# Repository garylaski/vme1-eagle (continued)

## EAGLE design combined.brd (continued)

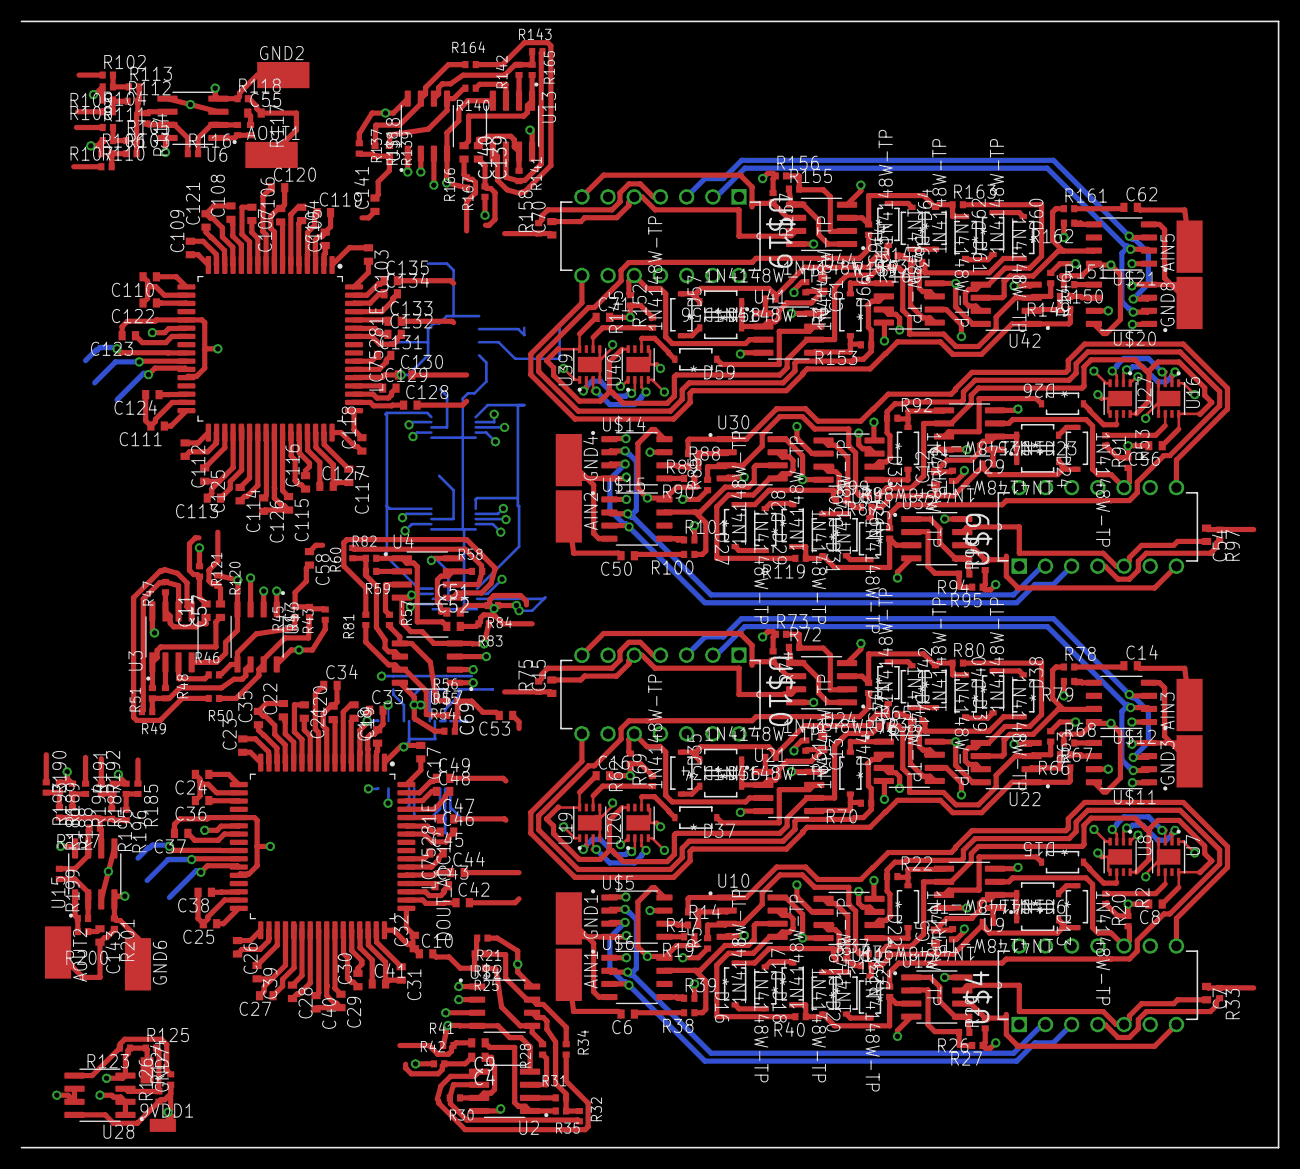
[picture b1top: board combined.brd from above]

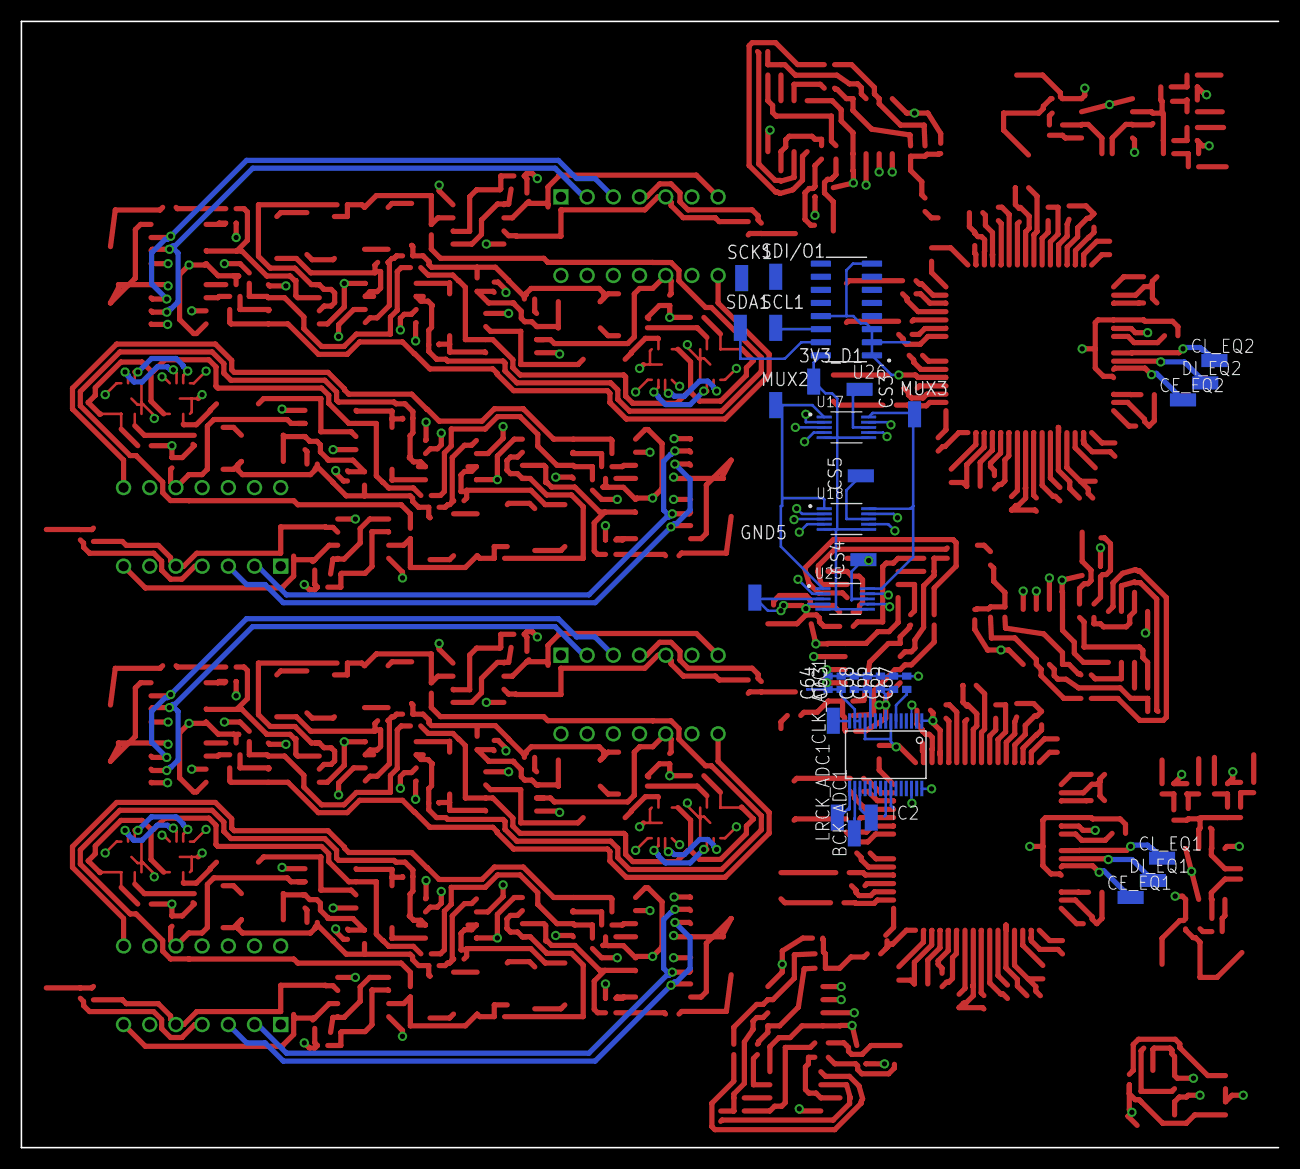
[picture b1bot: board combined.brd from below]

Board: 4 copper layers, 121.9 x 109.2 mm, 398 parts (33 on the bottom side), 337 nets.

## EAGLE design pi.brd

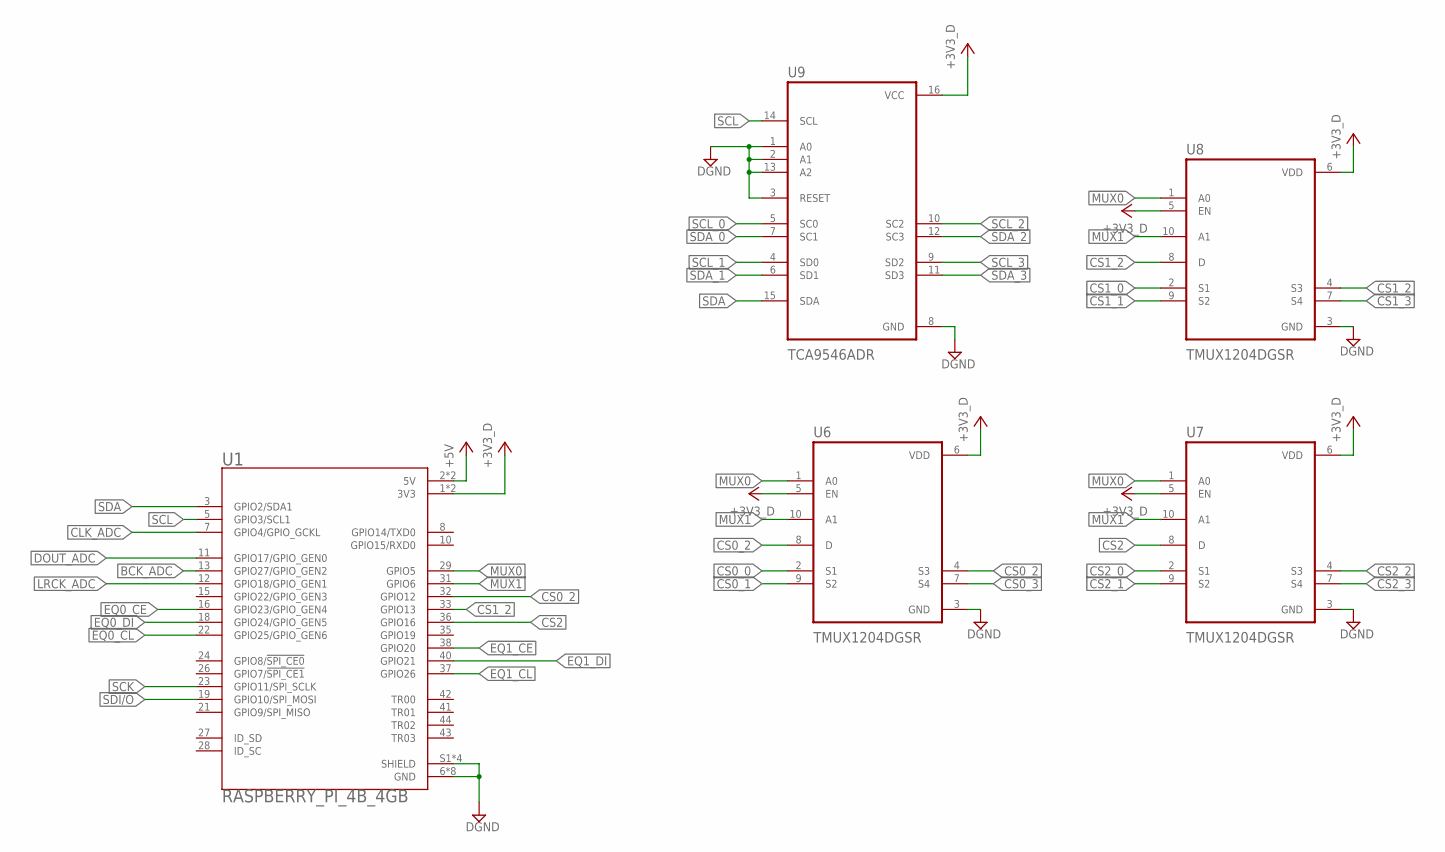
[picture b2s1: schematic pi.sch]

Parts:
U1: RASPBERRY_PI_4B_4GB; MODULE_RASPBERRY_PI_4B_4GB
U6, U7, U8: TMUX1204DGSR; SOP50P490X110-10N
U9: TCA9546ADR; SOIC127P600X175-16N

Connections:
5V: U1.2 (5V), U1.4 (5V)
+3V3: U1.1 (3V3), U1.17 (3V3), U6.5 (EN), U6.6 (VDD), U7.5 (EN), U7.6 (VDD), U8.5 (EN), U8.6 (VDD), U9.16 (VCC)
BCK_ADC: U1.13 (GPIO27/GPIO_GEN2)
CLK_ADC: U1.7 (GPIO4/GPIO_GCKL)
CS0_0: U6.2 (S1)
CS0_1: U6.9 (S2)
CS0_3: U6.7 (S4)
CS1_0: U8.2 (S1)
CS1_1: U8.9 (S2)
CS1_3: U8.7 (S4)
CS2: U1.36 (GPIO16), U7.8 (D)
CS2_0: U7.2 (S1)
CS2_1: U7.9 (S2)
CS2_2: U7.4 (S3)
CS2_3: U7.7 (S4)
DGND: U1.6 (GND), U1.9 (GND), U1.14 (GND), U1.20 (GND), U1.25 (GND), U1.30 (GND), U1.34 (GND), U1.39 (GND), U1.S1 (SHIELD), U1.S2 (SHIELD), U1.S3 (SHIELD), U1.S4 (SHIELD), U6.3 (GND), U7.3 (GND), U8.3 (GND), U9.1 (A0), U9.2 (A1), U9.3 (RESET), U9.8 (GND), U9.13 (A2)
DOUT_ADC: U1.11 (GPIO17/GPIO_GEN0)
EQ0_CE: U1.16 (GPIO23/GPIO_GEN4)
EQ0_CL: U1.22 (GPIO25/GPIO_GEN6)
EQ0_DI: U1.18 (GPIO24/GPIO_GEN5)
EQ1_CE: U1.38 (GPIO20)
EQ1_CL: U1.37 (GPIO26)
EQ1_DI: U1.40 (GPIO21)
LRCK_ADC: U1.12 (GPIO18/GPIO_GEN1)
MUX0: U1.29 (GPIO5), U6.1 (A0), U7.1 (A0), U8.1 (A0)
MUX1: U1.31 (GPIO6), U6.10 (A1), U7.10 (A1), U8.10 (A1)
SCK: U1.23 (GPIO11/SPI_SCLK)
SCL: U1.5 (GPIO3/SCL1), U9.14 (SCL)
SCL_0: U9.5 (SC0)
SCL_1: U9.4 (SD0)
SCL_2: U9.10 (SC2)
SCL_3: U9.9 (SD2)
SDA: U1.3 (GPIO2/SDA1), U9.15 (SDA)
SDA_0: U9.7 (SC1)
SDA_1: U9.6 (SD1)
SDA_2: U9.12 (SC3)
SDA_3: U9.11 (SD3)
SDI/O: U1.19 (GPIO10/SPI_MOSI)

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
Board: 2 copper layers, 5 parts (0 on the bottom side), 10 nets, no tracks yet.
